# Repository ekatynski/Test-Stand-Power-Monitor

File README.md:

View this project on [CADLAB.io](https://cadlab.io/project/27045). 

# Test-Stand-Power-Monitor
A small board for cheaply and easily monitoring a motor test stand for a host of data types.

## Function
This board is capable of monitoring the following:
- 1x Voltage input
- 1x Hall Effect Sensor output (current measuring)
- 1x Displacement Sensor interface
- 1x UART (ESCs have UART telemetry output)
- 1x 1K RTD for temperature monitoring

In addition, this board is capable of operating a relay to control a contactor protecting the test stand power supply, as well as a CAN bus to interface with other sensory hardware in development utilizing CAN. In doing so, this board could monitor ESC power consumption, ESC temperature, ESC telemetry output, motor displacement, and eventually eRPM pending future hardware development. Prior test stand setups had used a Teensy 4.1 to monitor telemetry and perform no other function, so this board's development was to expand the amount of test stand monitoring that could be done cheaply while using a less costly and more available microcontroller in the event that it were damaged and required replacement.

## To-Do
Firmware to perform said monitoring has not yet been developed. This board utilizes an ESP32 microcontroller, chosen because it can be configured to communicate over WiFi out of the box, but I have not taken the time to write the C++ needed to make this board useful yet.

## Assembly Guide
If interested, an interactive BOM is available in this repo at `/bom/Test-Stand-Power-Monitor_2023-06-12_22-39-21.html`.

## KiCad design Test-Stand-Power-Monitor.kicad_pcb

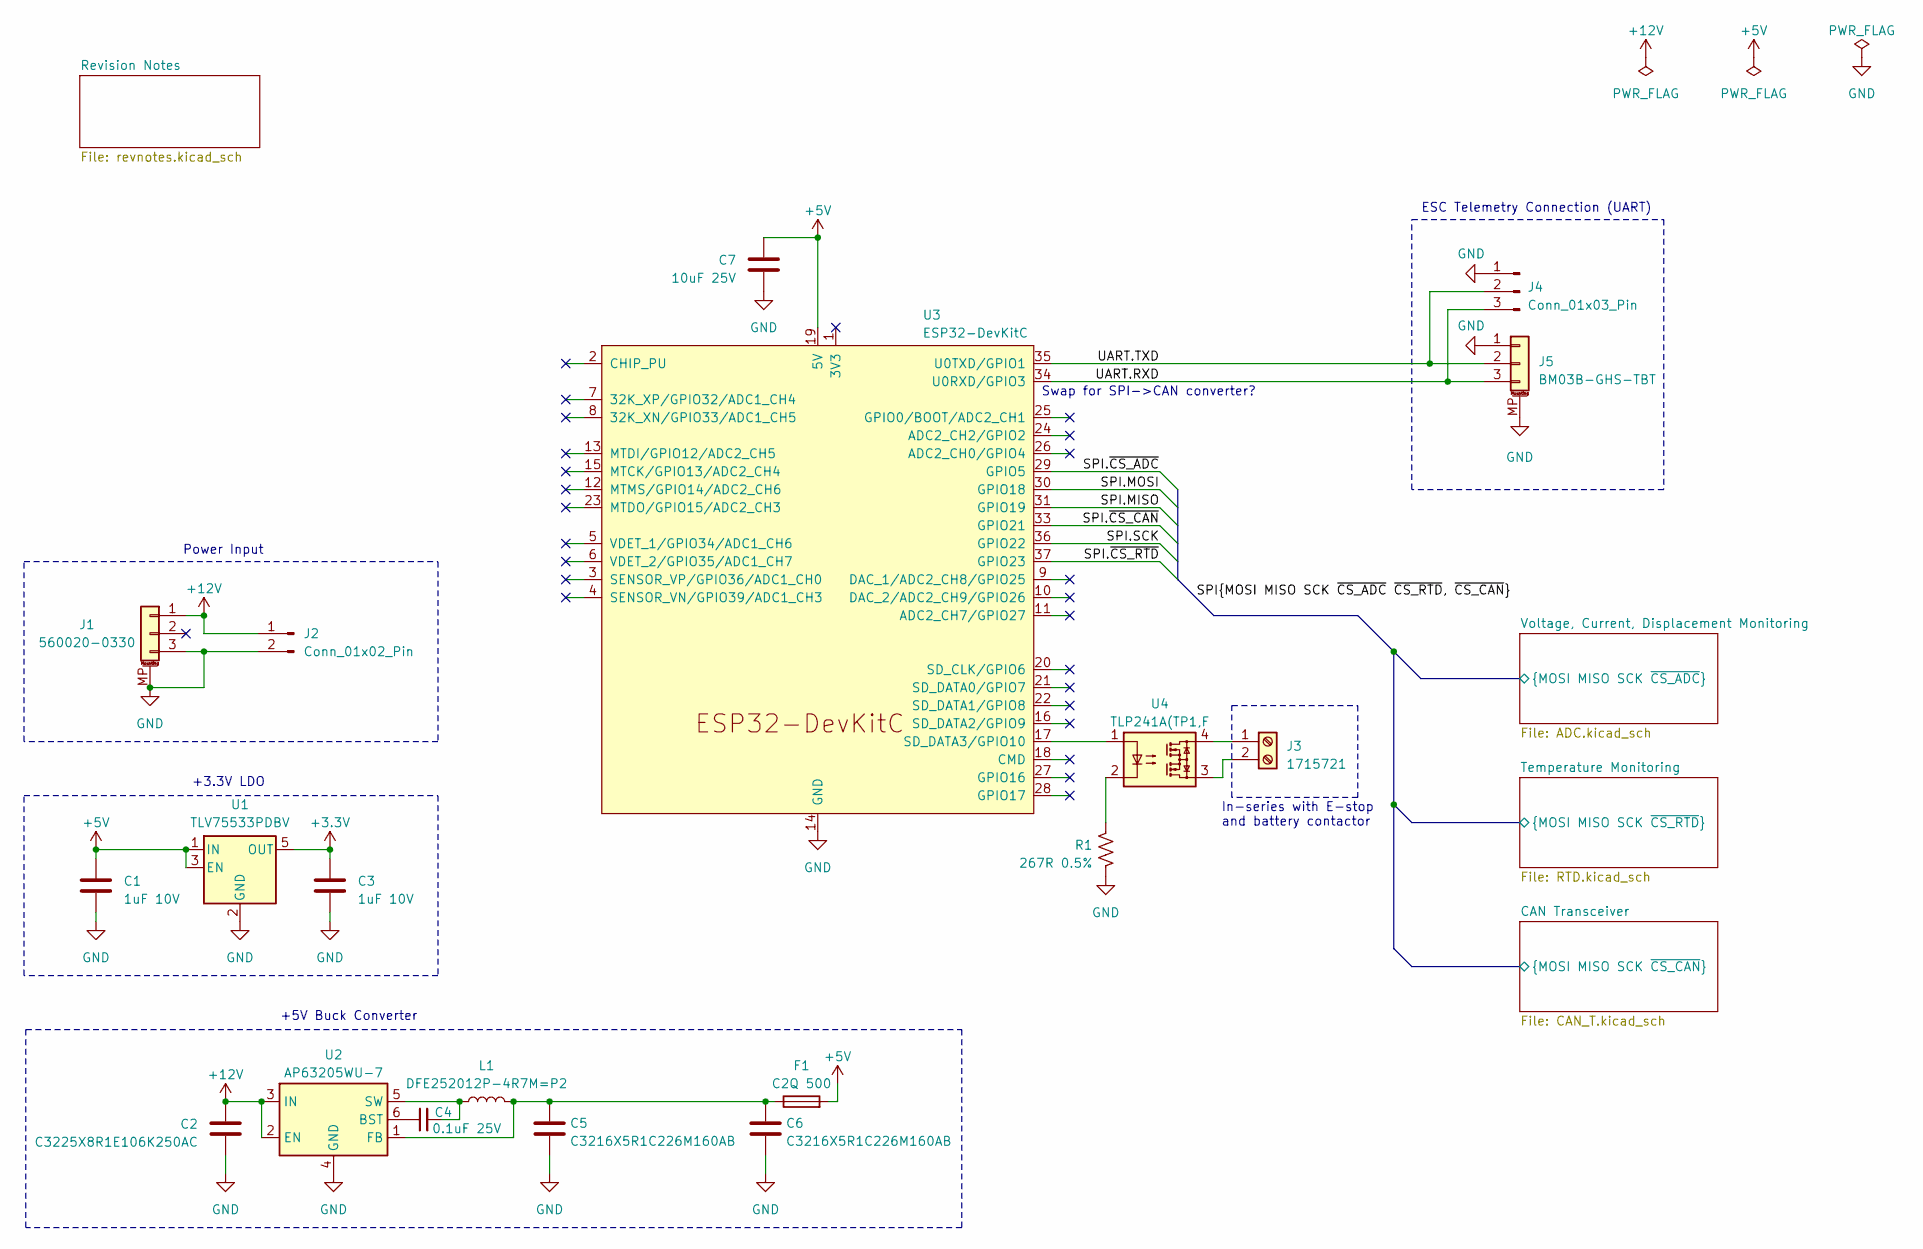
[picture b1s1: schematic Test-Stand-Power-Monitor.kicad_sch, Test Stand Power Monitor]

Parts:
C1, C3: 1uF 10V; C_0603_1608Metric_Pad1.08x0.95mm_HandSolder
C2: C3225X8R1E106K250AC; C_1210_3225Metric
C4: 0.1uF 25V; C_0402_1005Metric_Pad0.74x0.62mm_HandSolder
C5, C6: C3216X5R1C226M160AB; C_1206_3216Metric
C7: 10uF 25V; C_0603_1608Metric_Pad1.08x0.95mm_HandSolder
F1: C2Q 500; Fuse_0603_1608Metric
J1: 560020-0330; MOLEX_5600200330
J2: Conn_01x02_Pin; PinHeader_1x02_P2.54mm_Vertical
J3: 1715721; TerminalBlock_Phoenix_MKDS-1,5-2-5.08_1x02_P5.08mm_Horizont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
J4: Conn_01x03_Pin; PinHeader_1x03_P2.54mm_Vertical
J5: BM03B-GHS-TBT; JST_GH_BM03B-GHS-TBT_1x03-1MP_P1.25mm_Vertical
L1: DFE252012P-4R7M=P2; L_1008_2520Metric_Pad1.43x2.20mm_HandSolder
R1: 267R 0.5%; R_0402_1005Metric_Pad0.72x0.64mm_HandSolder
U1: TLV75533PDBV; SOT-23-5
U2: AP63205WU-7; TSOT-23-6
U3: ESP32-DevKitC
U4: TLP241A(TP1,F; OnSemi_CASE100CY

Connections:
+3.3V: C3.1, U1.5 (OUT); also elsewhere on the board
+5V: C1.1, C7.1, F1.2, U1.1 (IN), U1.3 (EN), U3.19 (5V); also elsewhere on the board
+12V: C2.1, J1.1, J2.1, U2.2 (EN), U2.3 (IN); also elsewhere on the board
/SPI.MISO: U3.31 (GPIO19); also elsewhere on the board
/SPI.MOSI: U3.30 (GPIO18); also elsewhere on the board
/SPI.SCK: U3.36 (GPIO22); also elsewhere on the board
/SPI.~CS_ADC: U3.29 (GPIO5); also elsewhere on the board
/SPI.~CS_CAN: U3.33 (GPIO21); also elsewhere on the board
/SPI.~CS_RTD: U3.37 (GPIO23); also elsewhere on the board
/UART.RXD: J4.3, J5.3, U3.34 (U0RXD/GPIO3)
/UART.TXD: J4.2, J5.2, U3.35 (U0TXD/GPIO1)
GND: C1.2, C2.2, C3.2, C5.2, C6.2, C7.2, J1.3, J1.MP (MountPin), J2.2, J4.1, J5.1, J5.MP (MountPin), R1.2, U1.2 (GND), U2.4 (GND), U3.14 (GND), U3.32 (GND), U3.38 (GND); also elsewhere on the board
unnamed: J3.1, U4.4
unnamed: J3.2, U4.3
unnamed: R1.1, U4.2
unnamed: C4.1, U2.6 (BST)
unnamed: C5.1, C6.1, F1.1, L1.2, U2.1 (FB)
unnamed: C4.2, L1.1, U2.5 (SW)
unnamed: U3.17 (SD_DATA3/GPIO10), U4.1

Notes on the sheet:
In-series with E-stop and battery contactor
Power Input
+3.3V LDO
ESC Telemetry Connection (UART)
+5V Buck Converter
Swap for SPI->CAN converter?

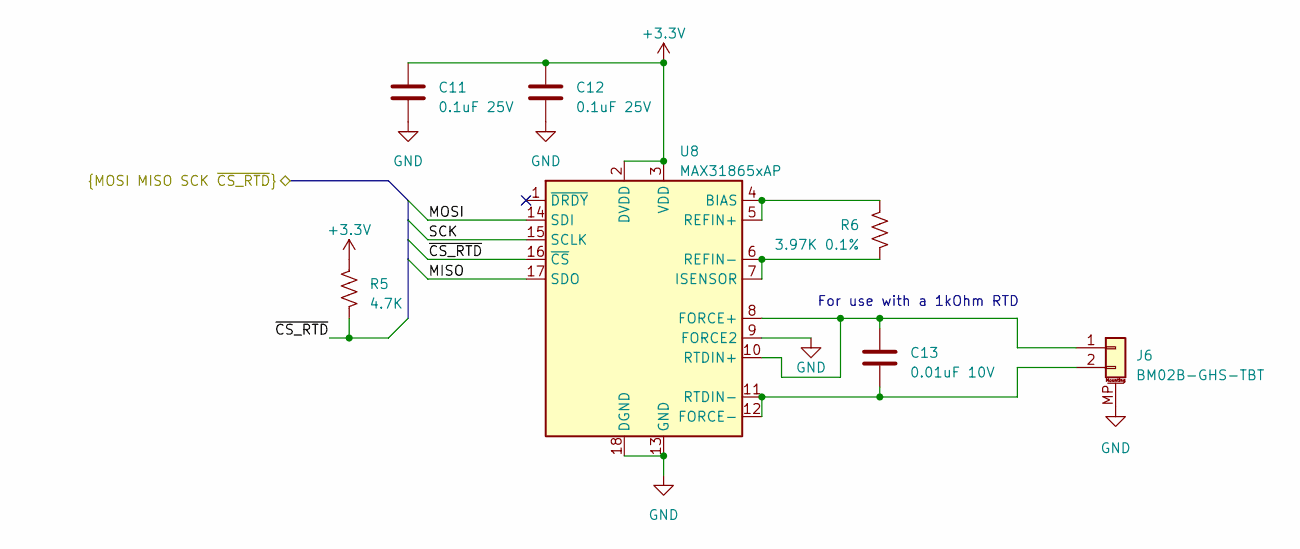
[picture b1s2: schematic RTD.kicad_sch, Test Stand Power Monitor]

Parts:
C11, C12: 0.1uF 25V; C_0402_1005Metric_Pad0.74x0.62mm_HandSolder
C13: 0.01uF 10V; C_0402_1005Metric_Pad0.74x0.62mm_HandSolder
J6: BM02B-GHS-TBT; JST_GH_BM02B-GHS-TBT_1x02-1MP_P1.25mm_Vertical
R5: 4.7K; R_0402_1005Metric_Pad0.72x0.64mm_HandSolder
R6: 3.97K 0.1%; R_0402_1005Metric_Pad0.72x0.64mm_HandSolder
U8: MAX31865xAP; SSOP-20_5.3x7.2mm_P0.65mm

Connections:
+3.3V: C11.1, C12.1, R5.1, U8.2 (DVDD), U8.3 (VDD); also elsewhere on the board
/SPI.MISO: U8.17 (SDO); also elsewhere on the board
/SPI.MOSI: U8.14 (SDI); also elsewhere on the board
/SPI.SCK: U8.15 (SCLK); also elsewhere on the board
/SPI.~CS_RTD: R5.2, U8.16 (~CS); also elsewhere on the board
GND: C11.2, C12.2, J6.MP (MountPin), U8.9 (FORCE2), U8.13 (GND), U8.18 (DGND), U8.19 (GND); also elsewhere on the board
unnamed: C13.1, J6.1, U8.8 (FORCE+), U8.10 (RTDIN+)
unnamed: C13.2, J6.2, U8.11 (RTDIN-), U8.12 (FORCE-)
unnamed: R6.1, U8.4 (BIAS), U8.5 (REFIN+)
unnamed: R6.2, U8.6 (REFIN-), U8.7 (ISENSOR)

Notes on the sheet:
For use with a 1kOhm RTD

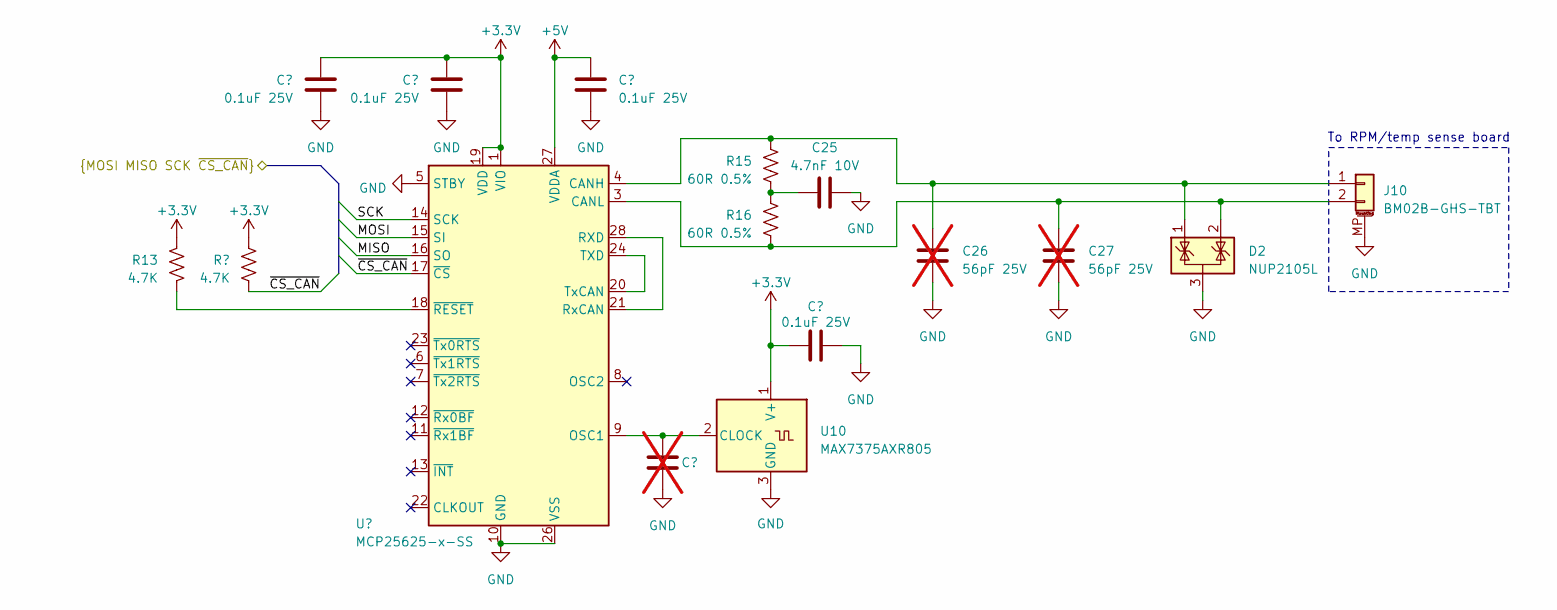
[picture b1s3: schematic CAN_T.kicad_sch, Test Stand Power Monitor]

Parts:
C20, C21, C22, C24: 0.1uF 25V; C_0402_1005Metric_Pad0.74x0.62mm_HandSolder
C23: C_0402_1005Metric_Pad0.74x0.62mm_HandSolder; not fitted
C25: 4.7nF 10V; C_0402_1005Metric_Pad0.74x0.62mm_HandSolder
C26, C27: 56pF 25V; C_0402_1005Metric_Pad0.74x0.62mm_HandSolder; not fitted
D2: NUP2105L; SOT-23
J10: BM02B-GHS-TBT; JST_GH_BM02B-GHS-TBT_1x02-1MP_P1.25mm_Vertical
R13, R14: 4.7K; R_0402_1005Metric_Pad0.72x0.64mm_HandSolder
R15, R16: 60R 0.5%; R_0603_1608Metric_Pad0.98x0.95mm_HandSolder
U9: MCP25625-x-SS; SSOP-28_5.3x10.2mm_P0.65mm
U10: MAX7375AXR805; SOT-323_SC-70

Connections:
+3.3V: C20.1, C21.1, C24.1, R13.1, R14.1, U9.1 (VIO), U9.19 (VDD), U10.1 (V+); also elsewhere on the board
+5V: C22.1, U9.27 (VDDA); also elsewhere on the board
/CAN Transceiver/CAN+: C26.2, D2.1 (K), J10.1, R15.1, U9.4 (CANH)
/CAN Transceiver/CAN-: C27.2, D2.2 (K), J10.2, R16.2, U9.3 (CANL)
/SPI.MISO: U9.16 (SO); also elsewhere on the board
/SPI.MOSI: U9.15 (SI); also elsewhere on the board
/SPI.SCK: U9.14 (SCK); also elsewhere on the board
/SPI.~CS_CAN: R14.2, U9.17 (~CS); also elsewhere on the board
GND: C20.2, C21.2, C22.2, C23.2, C24.2, C25.2, C26.1, C27.1, D2.3 (A), J10.MP (MountPin), U9.5 (STBY), U9.10 (GND), U9.26 (VSS), U10.3 (GND); also elsewhere on the board
unnamed: C25.1, R15.2, R16.1
unnamed: U9.21 (RxCAN), U9.28 (RXD)
unnamed: U9.20 (TxCAN), U9.24 (TXD)
unnamed: R13.2, U9.18 (~RESET)
unnamed: C23.1, U9.9 (OSC1), U10.2 (CLOCK)

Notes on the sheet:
To RPM/temp sense board

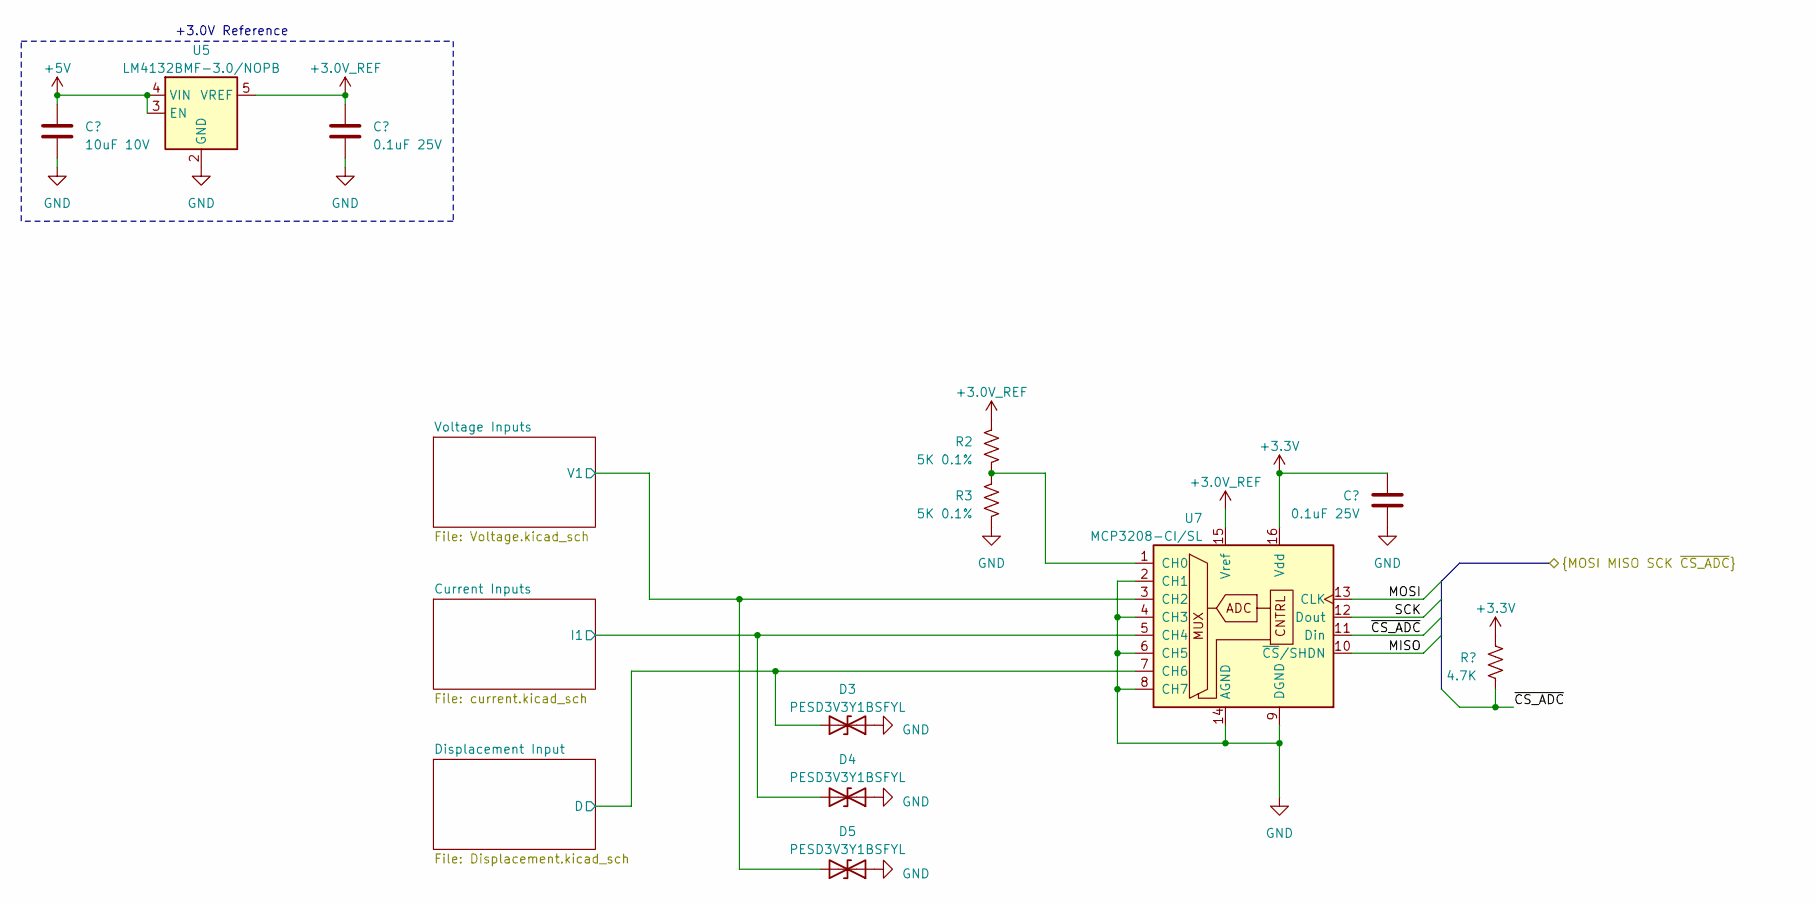
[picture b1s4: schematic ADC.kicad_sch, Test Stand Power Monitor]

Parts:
C8: 10uF 10V; C_0603_1608Metric_Pad1.08x0.95mm_HandSolder
C9, C10: 0.1uF 25V; C_0402_1005Metric_Pad0.74x0.62mm_HandSolder
D3, D4, D5: PESD3V3Y1BSFYL; D_0201_0603Metric
R2, R3: 5K 0.1%; R_0402_1005Metric_Pad0.72x0.64mm_HandSolder
R4: 4.7K; R_0402_1005Metric_Pad0.72x0.64mm_HandSolder
U5: LM4132BMF-3.0/NOPB; SOT-23-5
U7: MCP3208-CI/SL; SOIC-16_3.9x9.9mm_P1.27mm

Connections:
+3.0V_REF: C9.1, R2.1, U5.5 (VREF), U7.15 (Vref)
+3.3V: C10.1, R4.1, U7.16 (Vdd); also elsewhere on the board
+5V: C8.1, U5.3 (EN), U5.4 (VIN); also elsewhere on the board
/SPI.MISO: U7.10 (~CS/SHDN); also elsewhere on the board
/SPI.MOSI: U7.13 (CLK); also elsewhere on the board
/SPI.SCK: U7.12 (Dout); also elsewhere on the board
/SPI.~CS_ADC: R4.2, U7.11 (Din); also elsewhere on the board
/Voltage, Current, Displacement Monitoring/Current Inputs/I1: D4.2 (A2), U7.5 (CH4); also elsewhere on the board
/Voltage, Current, Displacement Monitoring/Displacement Input/D: D3.2 (A2), U7.7 (CH6); also elsewhere on the board
/Voltage, Current, Displacement Monitoring/Voltage Inputs/V1: D5.2 (A2), U7.3 (CH2); also elsewhere on the board
GND: C8.2, C9.2, C10.2, D3.1 (A1), D4.1 (A1), D5.1 (A1), R3.2, U5.2 (GND), U7.2 (CH1), U7.4 (CH3), U7.6 (CH5), U7.8 (CH7), U7.9 (DGND), U7.14 (AGND); also elsewhere on the board
unnamed: R2.2, R3.1, U7.1 (CH0)

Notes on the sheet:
+3.0V Reference

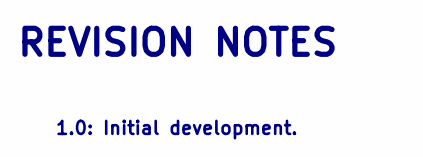
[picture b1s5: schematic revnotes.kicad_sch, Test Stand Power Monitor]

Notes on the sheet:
REVISION NOTES
1.0: Initial development.

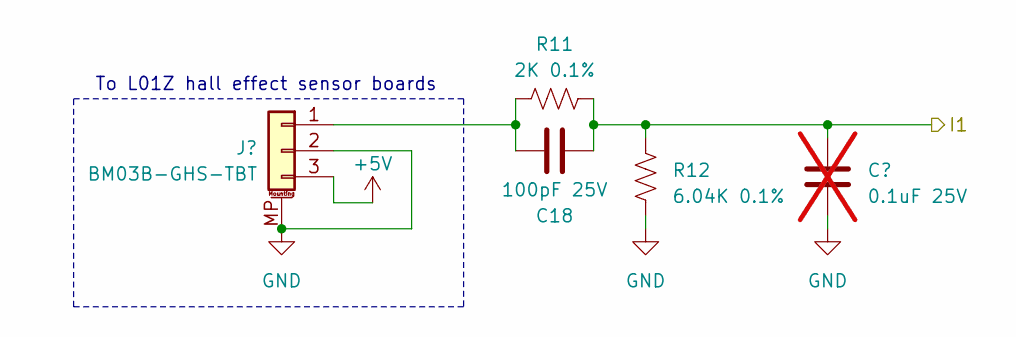
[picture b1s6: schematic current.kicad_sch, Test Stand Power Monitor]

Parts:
C18: 100pF 25V; C_0402_1005Metric_Pad0.74x0.62mm_HandSolder
C19: 0.1uF 25V; C_0402_1005Metric_Pad0.74x0.62mm_HandSolder; not fitted
J9: BM03B-GHS-TBT; JST_GH_BM03B-GHS-TBT_1x03-1MP_P1.25mm_Vertical
R11: 2K 0.1%; R_0402_1005Metric_Pad0.72x0.64mm_HandSolder
R12: 6.04K 0.1%; R_0402_1005Metric_Pad0.72x0.64mm_HandSolder

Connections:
+5V: J9.3; also elsewhere on the board
/Voltage, Current, Displacement Monitoring/Current Inputs/I1: C18.2, C19.1, R11.2, R12.1; also elsewhere on the board
GND: C19.2, J9.2, J9.MP (MountPin), R12.2; also elsewhere on the board
unnamed: C18.1, J9.1, R11.1

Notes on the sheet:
To L01Z hall effect sensor boards

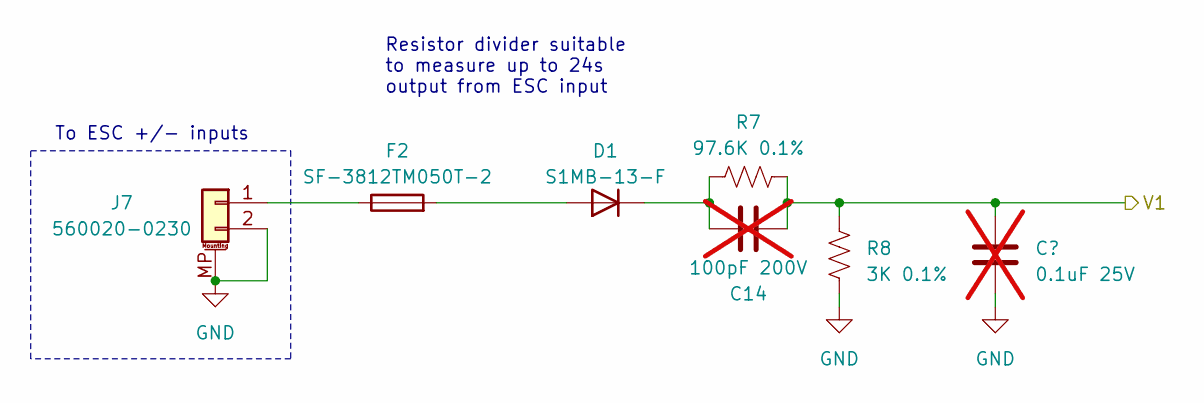
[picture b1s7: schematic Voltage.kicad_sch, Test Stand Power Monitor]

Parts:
C14: 100pF 200V; C_0603_1608Metric_Pad1.08x0.95mm_HandSolder; not fitted
C15: 0.1uF 25V; C_0402_1005Metric_Pad0.74x0.62mm_HandSolder; not fitted
D1: S1MB-13-F; D_SMA-SMB_Universal_Handsoldering
F2: SF-3812TM050T-2
J7: 560020-0230; MOLEX_5600200230
R7: 97.6K 0.1%; R_0805_2012Metric_Pad1.20x1.40mm_HandSolder
R8: 3K 0.1%; R_0402_1005Metric_Pad0.72x0.64mm_HandSolder

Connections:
/Voltage, Current, Displacement Monitoring/Voltage Inputs/V1: C14.2, C15.1, R7.2, R8.1; also elsewhere on the board
GND: C15.2, J7.2, J7.MP (MountPin), R8.2; also elsewhere on the board
unnamed: D1.2 (A), F2.2
unnamed: C14.1, D1.1 (K), R7.1
unnamed: F2.1, J7.1

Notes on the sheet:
Resistor divider suitable to measure up to 24s output from ESC input
To ESC +/- inputs

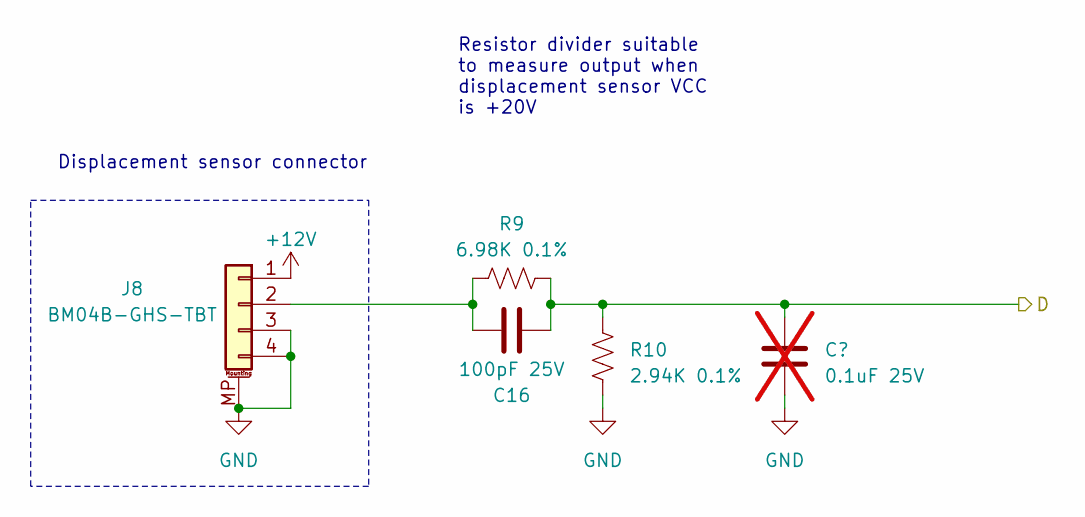
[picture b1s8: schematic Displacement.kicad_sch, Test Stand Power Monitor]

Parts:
C16: 100pF 25V; C_0402_1005Metric_Pad0.74x0.62mm_HandSolder
C17: 0.1uF 25V; C_0402_1005Metric_Pad0.74x0.62mm_HandSolder; not fitted
J8: BM04B-GHS-TBT; JST_GH_BM04B-GHS-TBT_1x04-1MP_P1.25mm_Vertical
R9: 6.98K 0.1%; R_0402_1005Metric_Pad0.72x0.64mm_HandSolder
R10: 2.94K 0.1%; R_0402_1005Metric_Pad0.72x0.64mm_HandSolder

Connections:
+12V: J8.1; also elsewhere on the board
/Voltage, Current, Displacement Monitoring/Displacement Input/D: C16.2, C17.1, R9.2, R10.1; also elsewhere on the board
GND: C17.2, J8.3, J8.4, J8.MP (MountPin), R10.2; also elsewhere on the board
unnamed: C16.1, J8.2, R9.1

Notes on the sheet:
Displacement sensor connector
Resistor divider suitable to measure output when displacement sensor VCC is +20V

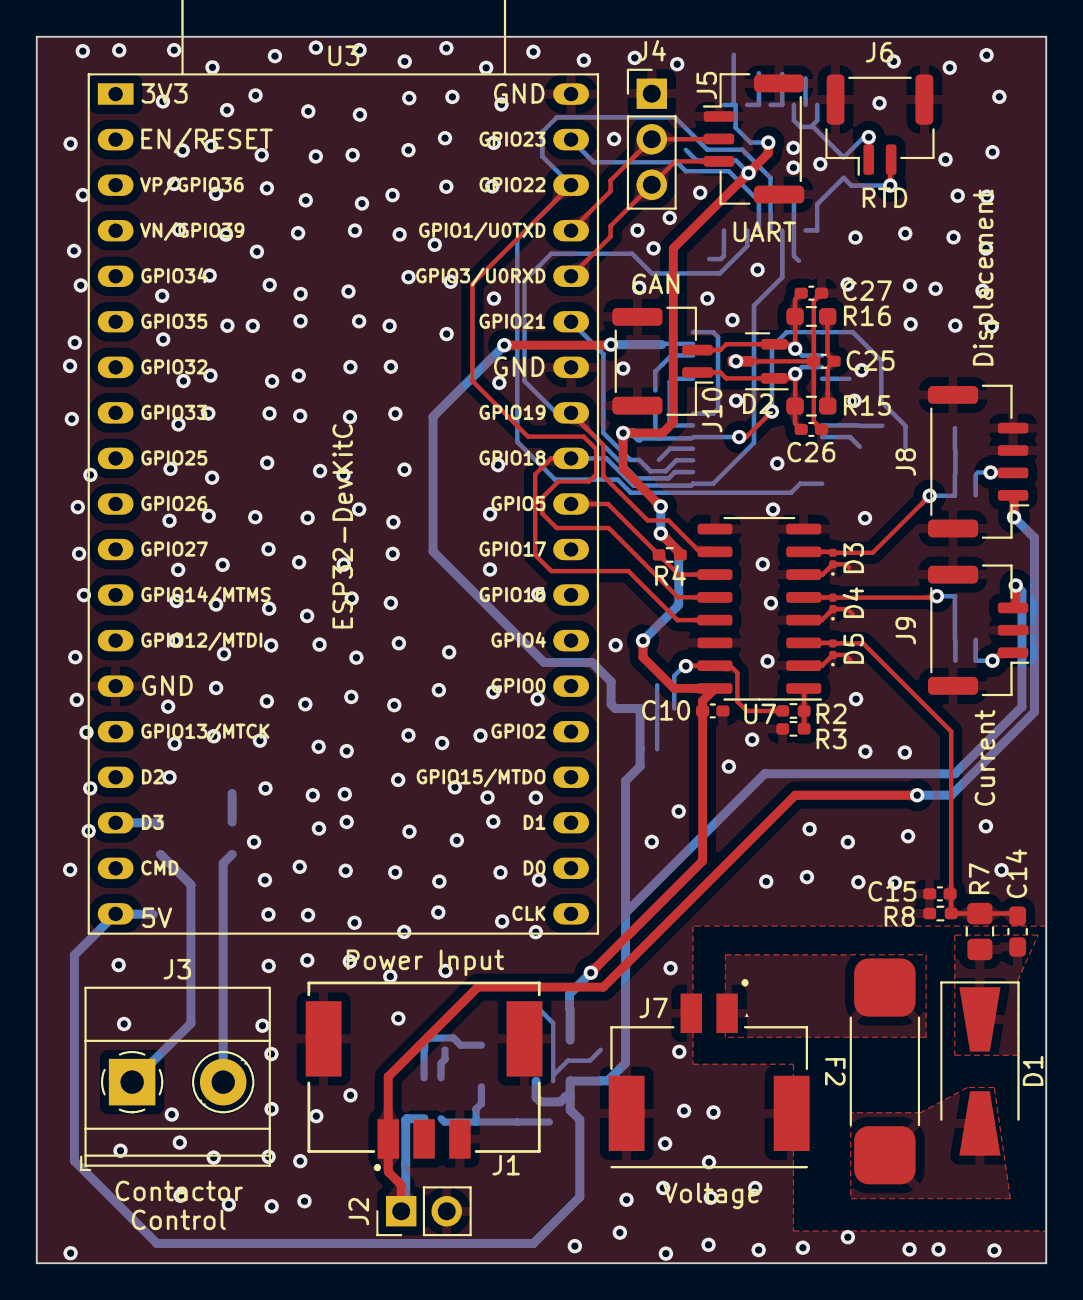
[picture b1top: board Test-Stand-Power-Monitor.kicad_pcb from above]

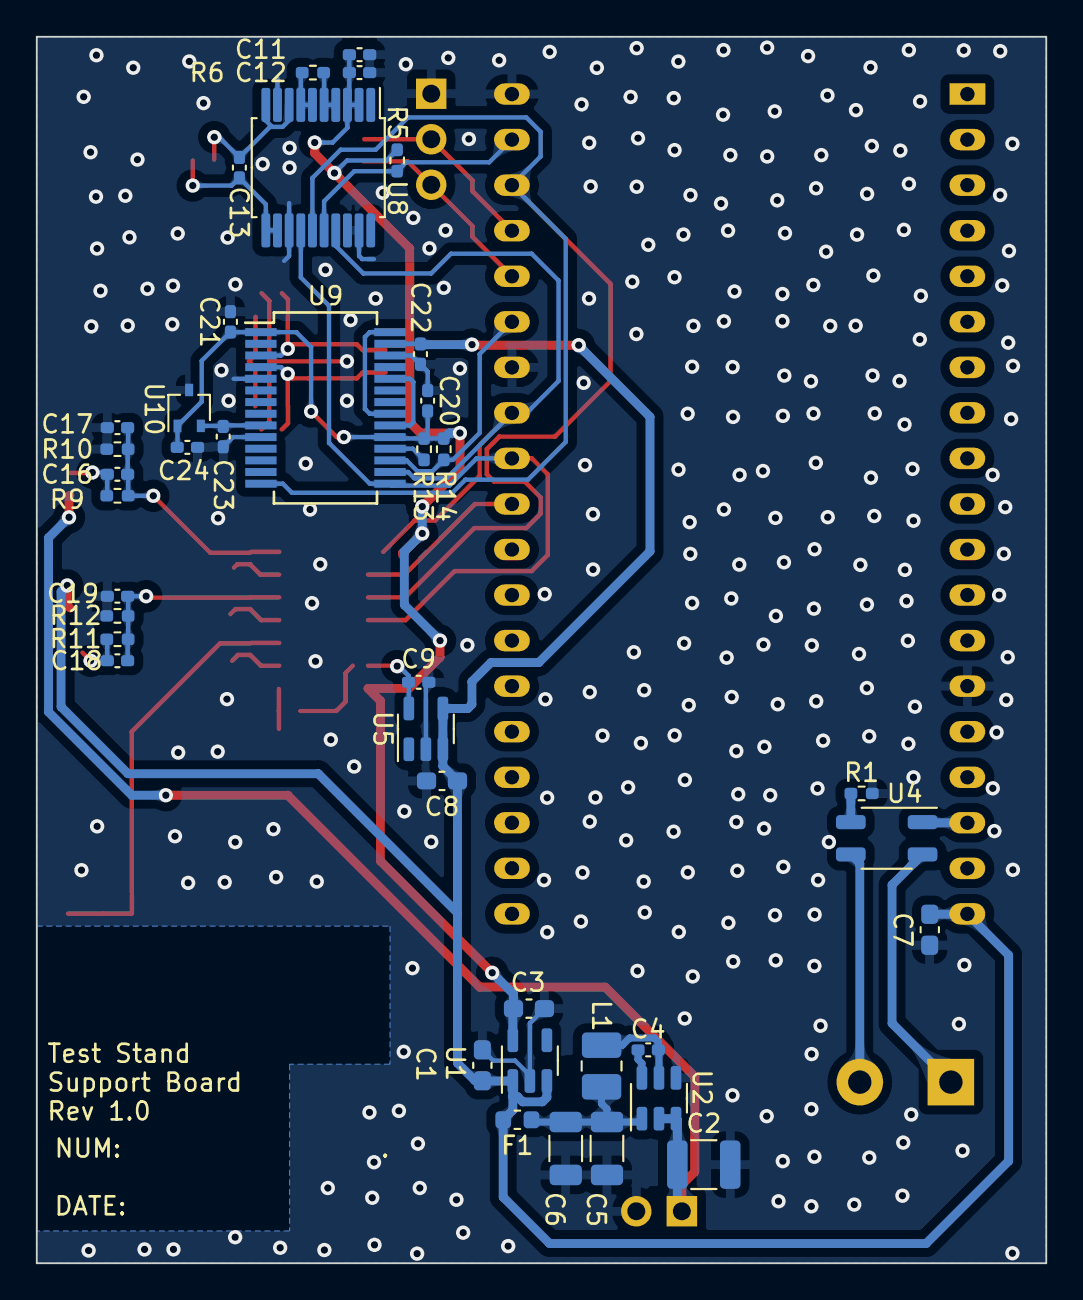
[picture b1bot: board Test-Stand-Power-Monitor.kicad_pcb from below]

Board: 4 copper layers, 56.3 x 68.4 mm, 70 parts (39 on the bottom side), 40 nets.

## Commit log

2023-06-13 Backlink to CADLAB.io has been added.
2023-06-13 Mass-adding all project files from prior development.
2023-06-13 Generated assembly guide.
2023-06-13 Updated README.
2023-06-13 Marked two-pin header as DNI to prevent short risk for +12V after testing.
2023-06-13 Schematic re-render.
2023-08-09 Updated .gitignore file
2023-08-09 Removed old file backups
2023-08-09 Removed schematic backup files from git tracking
2023-08-09 Removed old assembly guide files
2023-08-09 Removed tracking for autosaved PCB file
2023-08-09 Removed unused schematic file.
2023-08-09 Imported updated files from office verison of this project
2023-08-09 Slight 3.3V power trace movement for improved ground pour
2023-08-09 Teardrop update
2023-08-09 Replotted schematic
